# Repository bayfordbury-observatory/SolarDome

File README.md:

# SolarDome

The new solar observation platform

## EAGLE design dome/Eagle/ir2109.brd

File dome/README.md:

A custom dome controller driving two 24V DC motors.

The shutter motor is connected via a cable, as the dome does not need to rotate past North for solar observations. This greatly simplified logic as the shutter can move in any position.

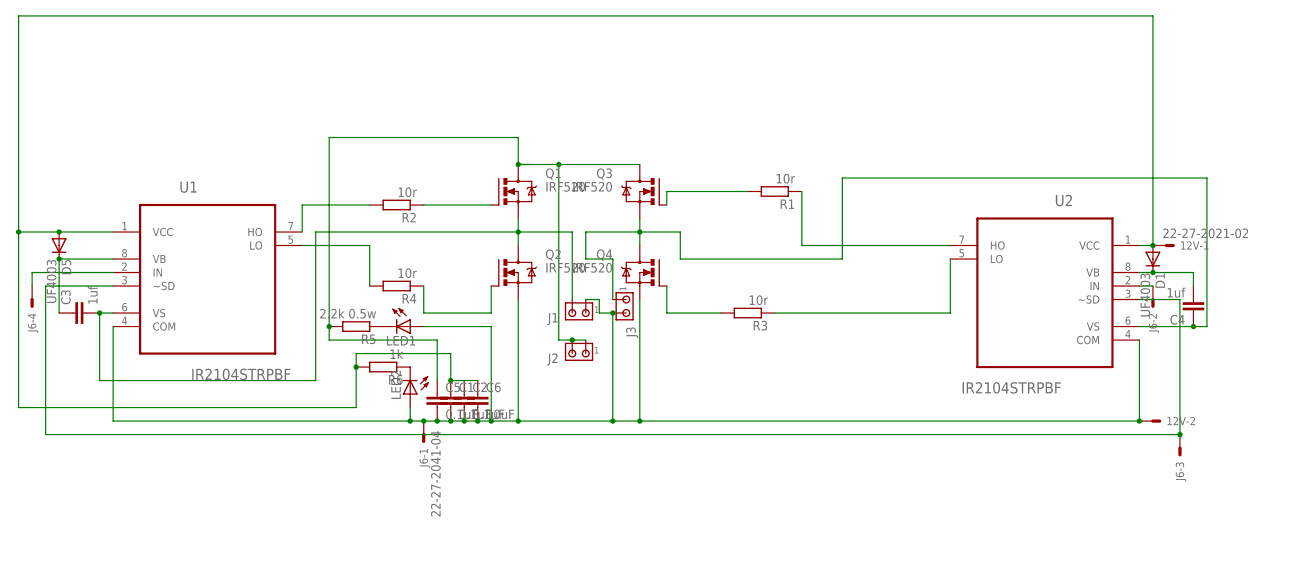
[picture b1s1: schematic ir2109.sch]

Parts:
12V: 22-27-2021-02; 6410-02
C1, C2, C5: 0.1uF; C0805
C3, C4: 1uf; C0805
C6: 10uF; C5B7.2
D1, D5: UF4003; DO41-10
J1, J2, J3: MTA02-156; 1X2MTA
J6: 22-27-2041-04; 6410-04
LED1, LED2: LEDCHIP-LED0603; CHIP-LED0603
Q1, Q2, Q3, Q4: IRF520; TO220BV
R1, R2, R3, R4: 10r; R0805
R5: 2.2k 0.5w; R1210
R6: 1k; R0805
U1, U2: IR2104STRPBF; SOIC127P600X175-8N

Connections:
12V: 12V.1, C1.1, C2.1, C6.1, D1.A, D5.A, R6.2, U1.1 (VCC), U2.1 (VCC)
24V: C5.1, J2.1, J2.2, Q1.D, Q3.D, R5.2
GND: 12V.2, C1.2, C2.2, C5.2, C6.2, J1.1, J3.2, J6.1, LED1.A, LED2.A, Q2.S, Q4.S, U1.4 (COM), U2.4 (COM)
HO1: R2.2, U1.7 (HO)
HO2: R1.1, U2.7 (HO)
IN1: J6.4, U1.2 (IN)
IN2: J6.2, U2.2 (IN)
LO1: R4.2, U1.5 (LO)
LO2: R3.1, U2.5 (LO)
M1: C3.2, J1.2, Q1.S, Q2.D, U1.6 (VS)
M2: C4.1, J3.1, Q3.S, Q4.D, U2.6 (VS)
unnamed: Q3.G, R1.2
unnamed: Q2.G, R4.1
unnamed: Q1.G, R2.1
unnamed: C3.1, D5.C, U1.8 (VB)
unnamed: LED1.C, R5.1
unnamed: Q4.G, R3.2
unnamed: LED2.C, R6.1
unnamed: C4.2, D1.C, U2.8 (VB)
SD: J6.3, U1.3 (~SD), U2.3 (~SD)

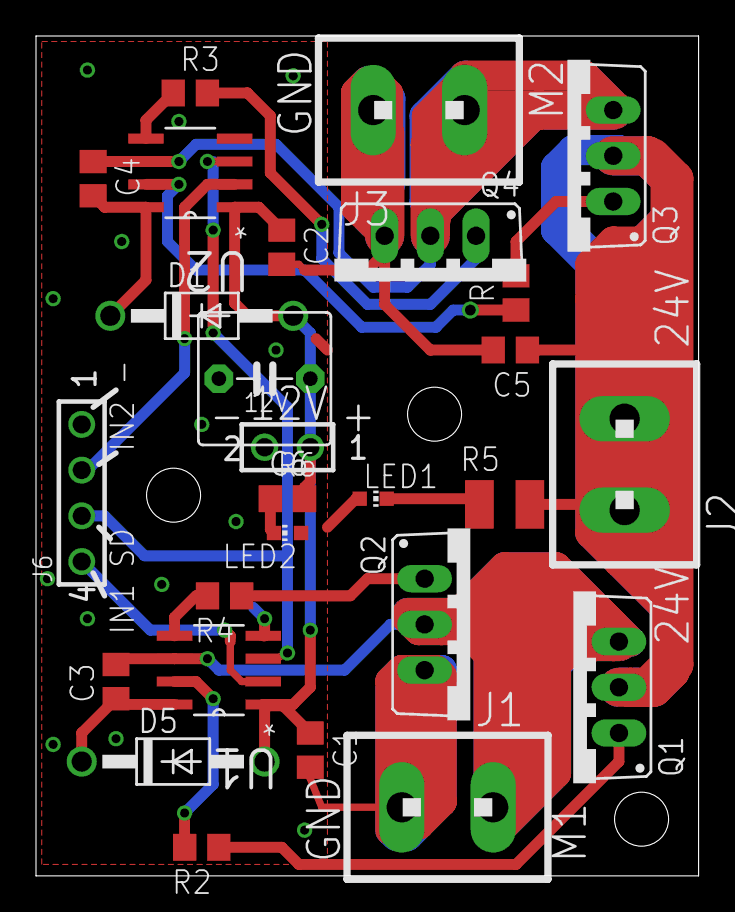
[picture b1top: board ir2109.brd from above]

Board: 2 copper layers, 36.8 x 46.7 mm, 27 parts (0 on the bottom side), 20 nets.

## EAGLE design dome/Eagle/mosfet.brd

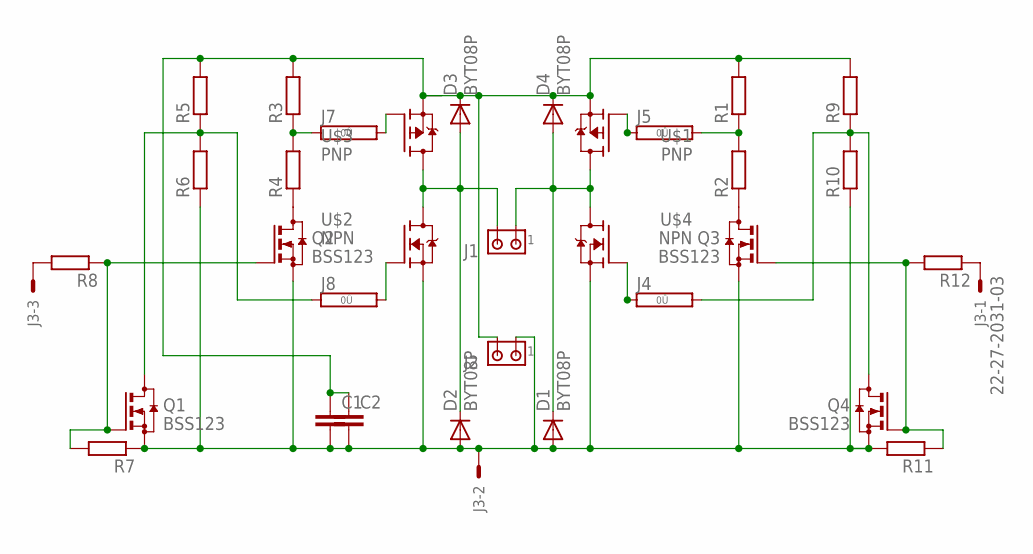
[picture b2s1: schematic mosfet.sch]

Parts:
C1, C2: C-EUC0805; C0805
D1, D2, D3, D4: BYT08P; TO220ACS
J1, J2: MTA02-156; 1X2MTA
J3: 22-27-2031-03; 6410-03
J4, J5, J7, J8: 0R; 0R/10
Q1, Q2, Q3, Q4: BSS123; SOT23
R1, R2, R3, R4, R5, R6, R7, R8, R9, R10, R11, R12: R-EU_R0805; R0805
U$1, U$3: PNP; TO-220
U$2, U$4: NPN; TO-247

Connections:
24V: C1.1, C2.1, D3.C, D4.C, J2.2, R1.2, R3.2, R5.2, R9.2, U$1.3 (S), U$3.3 (S)
GND: C1.2, C2.2, D1.A, D2.A, J2.1, J3.2, Q1.2 (S), Q2.2 (S), Q3.2 (S), Q4.2 (S), R6.1, R7.1, R10.1, R11.2, U$2.P$3 (S), U$4.P$3 (S)
M1: D2.C, D3.A, J1.2, U$2.P$2 (D), U$3.2 (D)
M2: D1.C, D4.A, J1.1, U$1.2 (D), U$4.P$2 (D)
unnamed: J5.1, U$1.1 (G)
unnamed: J7.2, U$3.1 (G)
unnamed: J3.3, R8.2
unnamed: Q2.3 (D), R4.1
unnamed: Q3.3 (D), R2.1
unnamed: J8.2, U$2.P$1 (G)
unnamed: J8.1, Q1.3 (D), R5.1, R6.2
unnamed: J7.1, R3.1, R4.2
unnamed: Q1.1 (G), Q2.1 (G), R7.2, R8.1
unnamed: J4.2, Q4.3 (D), R9.1, R10.2
unnamed: Q3.1 (G), Q4.1 (G), R11.1, R12.2
unnamed: J5.2, R1.1, R2.2
unnamed: J4.1, U$4.P$1 (G)
unnamed: J3.1, R12.1

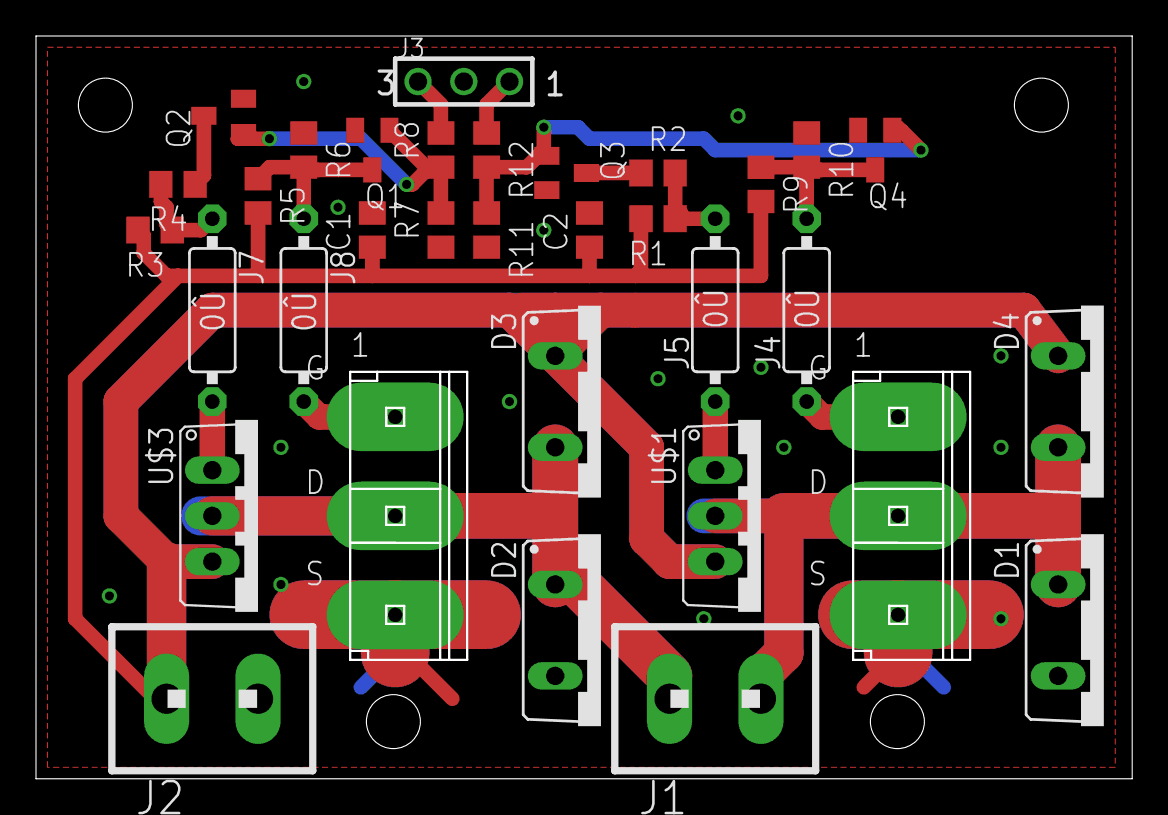
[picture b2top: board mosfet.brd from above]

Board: 2 copper layers, 60.8 x 41.1 mm, 33 parts (0 on the bottom side), 18 nets.

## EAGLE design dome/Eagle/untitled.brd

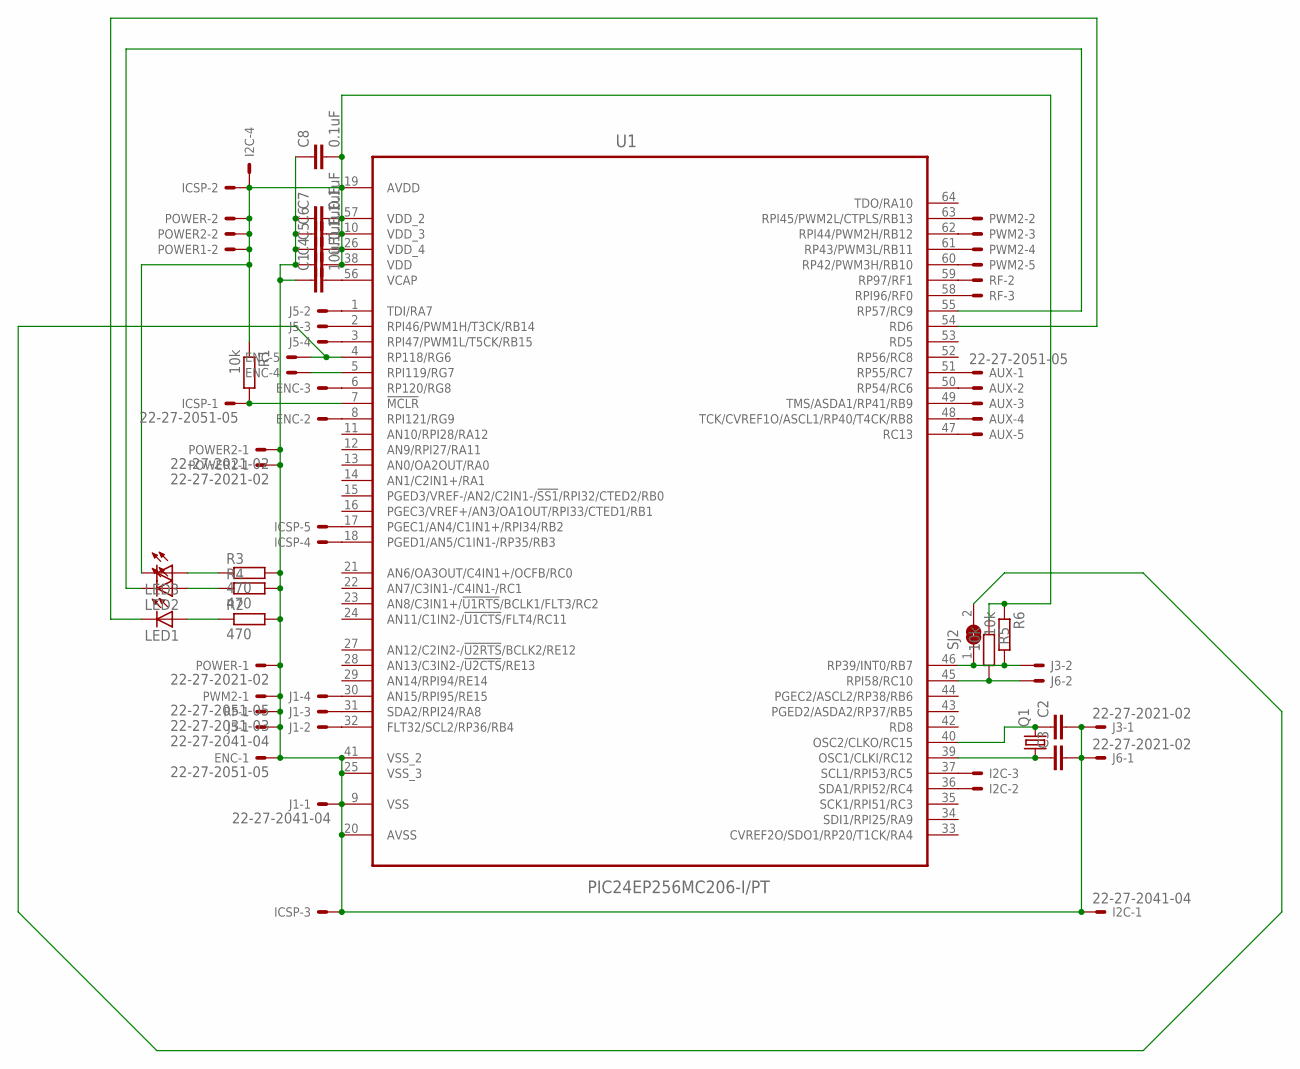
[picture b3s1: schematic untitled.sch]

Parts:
AUX: 22-27-2051-05; 6410-05
C1: 10uF; C0805
C2, C3: C-EUC0603; C0603
C4, C5, C6, C7, C8: 0.1uF; C0805
ENC: 22-27-2051-05; 6410-05
I2C: 22-27-2041-04; 6410-04
ICSP: 22-27-2051-05; 6410-05
J1, J5: 22-27-2041-04; 6410-04
J3, J6: 22-27-2021-02; 6410-02
LED1, LED2, LED3: LEDCHIP-LED0603; CHIP-LED0603
POWER, POWER1, POWER2: 22-27-2021-02; 6410-02
PWM2: 22-27-2051-05; 6410-05
Q1: CRYSTALHC49S; HC49/S
R1, R5, R6: 10k; R0805
R2, R3, R4: 470; R0805
RF: 22-27-2031-03; 6410-03
SJ2: SJ
U1: PIC24EP256MC206-I/PT; QFP50P1200X1200X120-64N

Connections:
GND: C1.1, C2.2, C3.2, C4.1, C5.1, C6.1, C7.1, C8.1, ENC.1, I2C.1, ICSP.3, J1.1, J3.1, J5.1, J6.1, POWER.1, POWER1.1, POWER2.1, PWM2.1, R2.2, R3.2, R4.2, RF.1, U1.9 (VSS), U1.20 (AVSS), U1.25 (VSS_3), U1.41 (VSS_2)
unnamed: C1.2, U1.56 (VCAP)
unnamed: ICSP.1, R1.2, U1.7 (!MCLR)
unnamed: C2.1, Q1.2, U1.40 (OSC2/CLKO/RC15)
unnamed: C3.1, Q1.1, U1.39 (OSC1/CLKI/RC12)
unnamed: ICSP.4, U1.18 (PGED1/AN5/C1IN1-/RP35/RB3)
unnamed: ICSP.5, U1.17 (PGEC1/AN4/C1IN1+/RPI34/RB2)
unnamed: I2C.2, U1.36 (SDA1/RPI52/RC4)
unnamed: I2C.3, U1.37 (SCL1/RPI53/RC5)
unnamed: PWM2.2, U1.63 (RPI45/PWM2L/CTPLS/RB13)
unnamed: PWM2.3, U1.62 (RPI44/PWM2H/RB12)
unnamed: PWM2.4, U1.61 (RP43/PWM3L/RB11)
unnamed: PWM2.5, U1.60 (RP42/PWM3H/RB10)
unnamed: RF.2, U1.59 (RP97/RF1)
unnamed: RF.3, U1.58 (RPI96/RF0)
unnamed: J5.2, U1.1 (TDI/RA7)
unnamed: J5.3, U1.2 (RPI46/PWM1H/T3CK/RB14)
unnamed: J5.4, U1.3 (RPI47/PWM1L/T5CK/RB15)
unnamed: ENC.5, SJ2.2, U1.4 (RP118/RG6)
unnamed: ENC.4, U1.5 (RPI119/RG7)
unnamed: ENC.3, U1.6 (RP120/RG8)
unnamed: ENC.2, U1.8 (RPI121/RG9)
unnamed: LED1.A, R2.1
unnamed: LED2.A, R4.1
unnamed: LED3.A, R3.1
unnamed: AUX.5, U1.47 (RC13)
unnamed: AUX.4, U1.48 (TCK/CVREF1O/ASCL1/RP40/T4CK/RB8)
unnamed: AUX.3, U1.49 (TMS/ASDA1/RP41/RB9)
unnamed: AUX.2, U1.50 (RP54/RC6)
unnamed: AUX.1, U1.51 (RP55/RC7)
unnamed: LED2.C, U1.55 (RP57/RC9)
unnamed: LED1.C, U1.54 (RD6)
unnamed: J1.2, U1.32 (FLT32/SCL2/RP36/RB4)
unnamed: J1.3, U1.31 (SDA2/RPI24/RA8)
unnamed: J3.2, R6.2, SJ2.1, U1.46 (RP39/INT0/RB7)
unnamed: J6.2, R5.2, U1.45 (RPI58/RC10)
unnamed: J1.4, U1.30 (AN15/RPI95/RE15)
VDD: C4.2, C5.2, C6.2, C7.2, C8.2, I2C.4, ICSP.2, LED3.C, POWER.2, POWER1.2, POWER2.2, R1.1, R5.1, R6.1, U1.10 (VDD_3), U1.19 (AVDD), U1.26 (VDD_4), U1.38 (VDD), U1.57 (VDD_2)

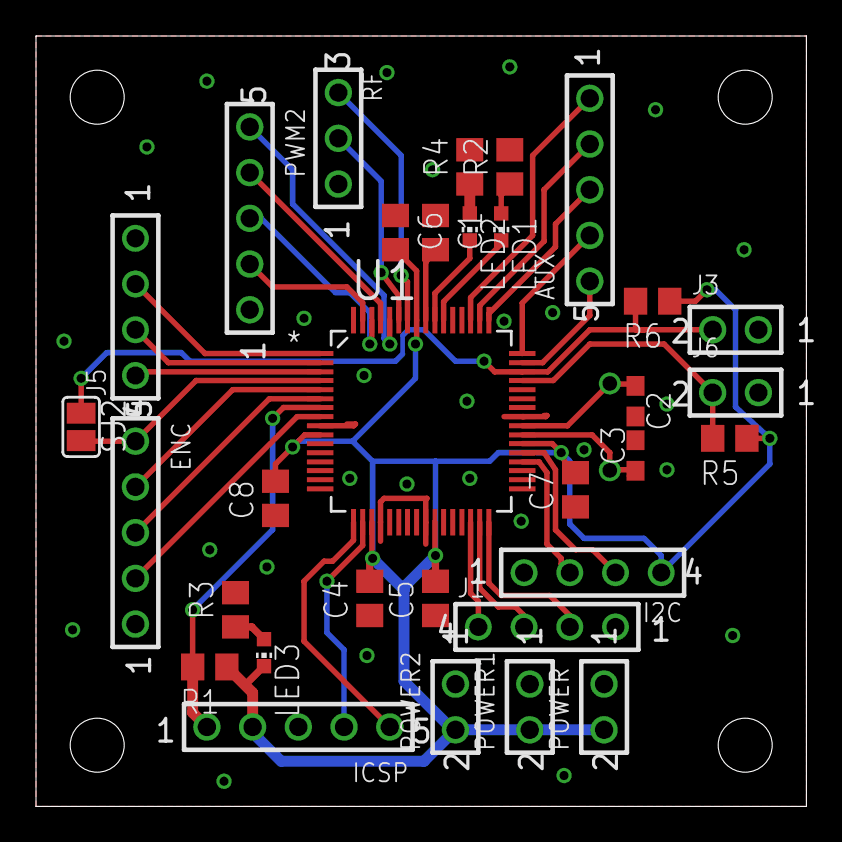
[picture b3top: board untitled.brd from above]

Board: 2 copper layers, 42.8 x 42.8 mm, 33 parts (1 on the bottom side), 38 nets.

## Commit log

2019-05-01 Initial upload
2019-05-01 align
